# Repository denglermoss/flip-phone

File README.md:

# Custom Phone Project

## Overview

Designing and building a custom cell phone from scratch — hardware (PCB, electronics), embedded firmware, cellular communication, and eventually mechanical/enclosure design. Candybar / single-board form factor (locked 2026-08-16 — flip/clamshell deferred to v2). Long-term vision: the phone is the hub of a personal ecosystem of USB-connected devices. See `docs/ref/problem-definition.md` for full architecture, MVP, risks, and ecosystem vision.

## Goals

- **Learning / Portfolio**: Deepen hardware and embedded systems skills; build something impressive.
- **Actually Usable**: End goal is a device that can make real phone calls on a real cellular network.
- **The Challenge**: Push beyond prior experience (microcontrollers, simple PCBs) into RF, cellular comms, power management, and eventually mechanical integration.

## Scope

### In Scope
- Custom PCB design (candybar / single-board — display via ZIF connector, no hinge flex)
- Microcontroller + off-the-shelf cellular module architecture
- Firmware: call handling, UI, contacts, power management
- Making real phone calls on a real network
- Mechanical/enclosure design (deferred — decided after electronics are proven)
- Hardware selection constrained to preserve USB connectivity for future ecosystem modules

### Out of Scope (for now)
- Custom cellular modem / baseband processor design
- FCC certification (prototype stage; revisit if moving toward production)
- App store, browser, or smartphone features (camera IS included on rev1 — see `docs/ref/project-log.md` 2026-08-16)
- Custom OS (will use RTOS or bare metal)
- Ecosystem module design (car system, etc.) — future projects, not this one

## Documentation

Full doc index and source-of-truth assignments in `AGENTS.md`. Key docs:

- `docs/ref/problem-definition.md` — architecture, MVP, risks, ecosystem vision
- `docs/ref/requirements.md` — functional & non-functional requirements
- `docs/ref/constraints.md` — technical, budget, regulatory constraints
- `docs/ref/project-log.md` — decision log (dated), phase breakdown
- `docs/ref/bom.md` — bill of materials with prices and links
- `docs/work/` — active planning docs (block-diagram, pin assignment, task tracker, schematic completion plan, UI design)
- `docs/archive/` — completed/superseded plans + all revisit prompts

## Status

**Phase 1 (Research & Component Selection) — Complete.** All guiding hardware decisions locked: MCU (STM32H743ZI), modem (SIM7600NA-H), codec (ALC5651-CG), display (ST7789V SPI TFT), keypad (SMD tactile switches), USB architecture (modem-direct tethering, no ULPI). Zephyr development environment set up (2026-06-29).

**Phase 2 (HAT-Based Prototype) — Complete.** MVP achieved (2026-07-13): MCU firmware places and receives VoLTE calls with audio on Mint LTE. Keypad integrated + verified (2026-07-18): standalone dialer — user types phone numbers and places real calls with no PC involvement. See `docs/ref/project-log.md` Phase Breakdown.

**Phase 3 (Schematic Design) — In Progress (2026-07-28).** All parts sourced with KiCad models (no consignment). Schematic approach: flat sheet + global labels, MPCIe modem form factor (primary), LGA fallback. **Per-sheet progress** (see `docs/work/schematic-completion-plan.md` for details): Power ✅, MCU ~92%, Modem ~90%, Codec ✅ (restored), Keypad ✅, Display main ~80% (backlight FET pending), Display daughter ~70%, SIM/SD ✅. ERC: 0 errors, 15 warnings. Remaining work tracked in `docs/work/schematic-completion-plan.md`; full Phase 3-5 plan in `docs/work/task-tracker.md`.

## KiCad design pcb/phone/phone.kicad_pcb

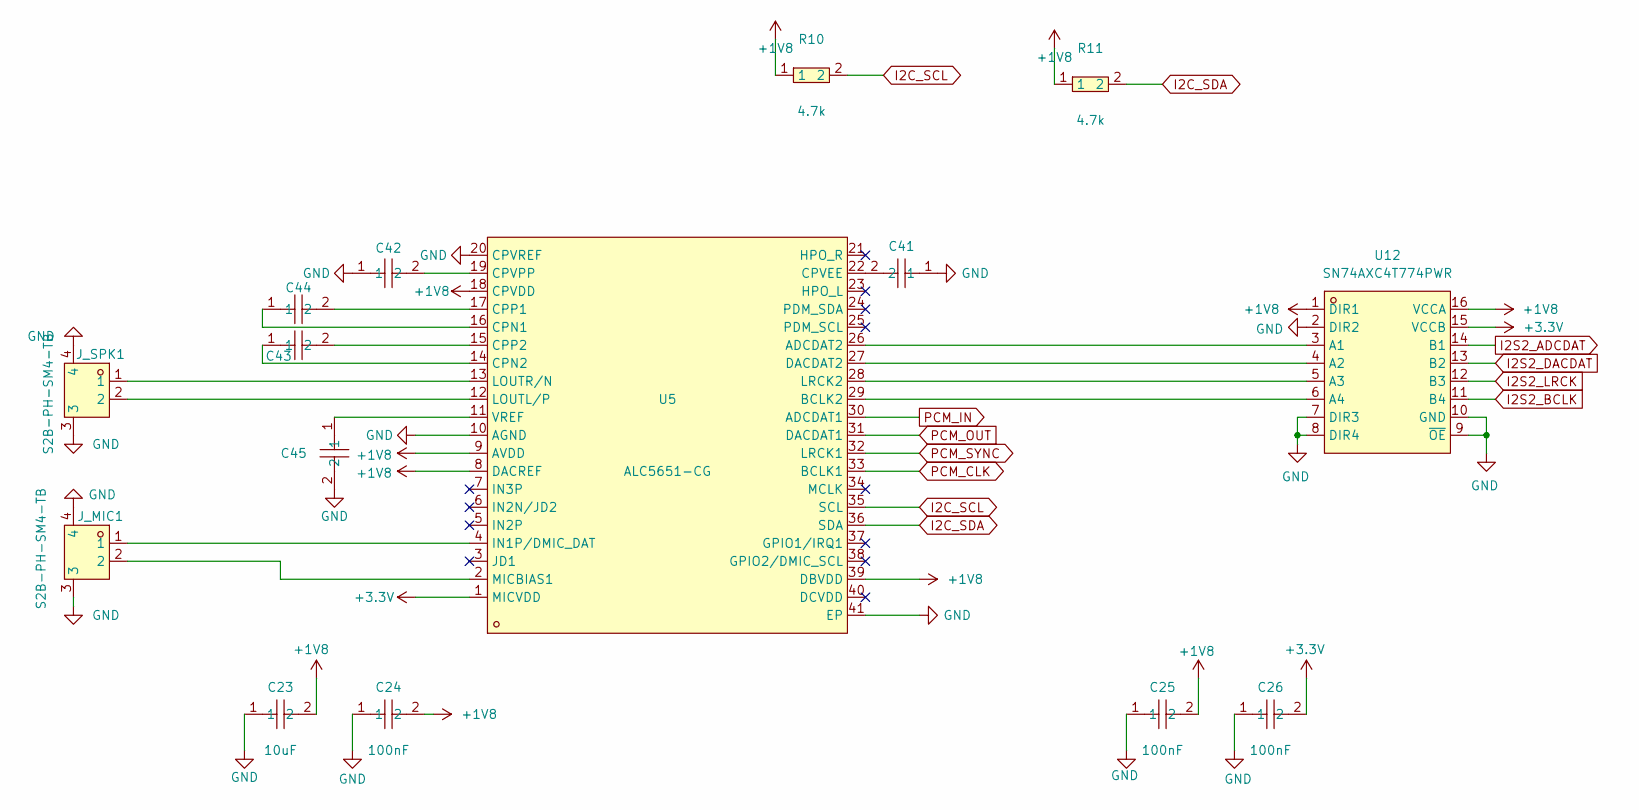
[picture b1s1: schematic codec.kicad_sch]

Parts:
C23: 10uF; C0805
C24, C25, C26: 100nF; C0603
C41, C42, C43, C44: CC0603KRX5R8BB225; C0603; MPN CC0603KRX5R8BB225; LCSC Part C309478
C45: GRM188R61C475KE11D; C0603; MPN GRM188R61C475KE11D; LCSC Part C77045
J_MIC1: S2B-PH-SM4-TB; CONN-SMD_P2.00_S2B-PH-SM4-TB-LF-SN
J_SPK1: S2B-PH-SM4-TB; CONN-SMD_P2.00_S2B-PH-SM4-TB-LF-SN
R10, R11: 4.7k; R0603
U5: ALC5651-CG; QFN-40_L5.0-W5.0-P0.40-BL-EP3.7
U12: SN74AXC4T774PWR; TSSOP-16_L5.0-W4.4-P0.65-LS6.4-TL; MPN SN74AXC4T774PWR; LCSC Part C1849453

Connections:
+1V8: C23.2, C24.2, C25.2, R10.1, R11.1, U5.8 (DACREF), U5.9 (AVDD), U5.18 (CPVDD), U5.39 (DBVDD), U12.1 (DIR1), U12.16 (VCCA); also elsewhere on the board
+3.3V: C26.2, U5.1 (MICVDD), U12.15 (VCCB); also elsewhere on the board
GND: C23.1, C24.1, C25.1, C26.1, C41.1, C42.1, C45.2, J_MIC1.3, J_MIC1.4, J_SPK1.3, J_SPK1.4, U5.10 (AGND), U5.20 (CPVREF), U5.41 (EP), U12.2 (DIR2), U12.7 (DIR3), U12.8 (DIR4), U12.9 (~OE), U12.10 (GND); also elsewhere on the board
I2C_SCL: R10.2, U5.35 (SCL); also elsewhere on the board
I2C_SDA: R11.2, U5.36 (SDA); also elsewhere on the board
I2S2_ADCDAT: U12.14 (B1); also elsewhere on the board
I2S2_BCLK: U12.11 (B4); also elsewhere on the board
I2S2_DACDAT: U12.13 (B2); also elsewhere on the board
I2S2_LRCK: U12.12 (B3); also elsewhere on the board
unnamed: C44.1, U5.16 (CPN1)
unnamed: C43.1, U5.14 (CPN2)
unnamed: C44.2, U5.17 (CPP1)
unnamed: C43.2, U5.15 (CPP2)
unnamed: C41.2, U5.22 (CPVEE)
unnamed: C42.2, U5.19 (CPVPP)
unnamed: J_MIC1.1, U5.4 (IN1P/DMIC_DAT)
unnamed: J_SPK1.2, U5.12 (LOUTL/P)
unnamed: J_SPK1.1, U5.13 (LOUTR/N)
unnamed: J_MIC1.2, U5.2 (MICBIAS1)
unnamed: C45.1, U5.11 (VREF)
unnamed: U5.26 (ADCDAT2), U12.3 (A1)
unnamed: U5.27 (DACDAT2), U12.4 (A2)
unnamed: U5.28 (LRCK2), U12.5 (A3)
unnamed: U5.29 (BCLK2), U12.6 (A4)
PCM_CLK: U5.33 (BCLK1); also elsewhere on the board
PCM_IN: U5.30 (ADCDAT1); also elsewhere on the board
PCM_OUT: U5.31 (DACDAT1); also elsewhere on the board
PCM_SYNC: U5.32 (LRCK1); also elsewhere on the board

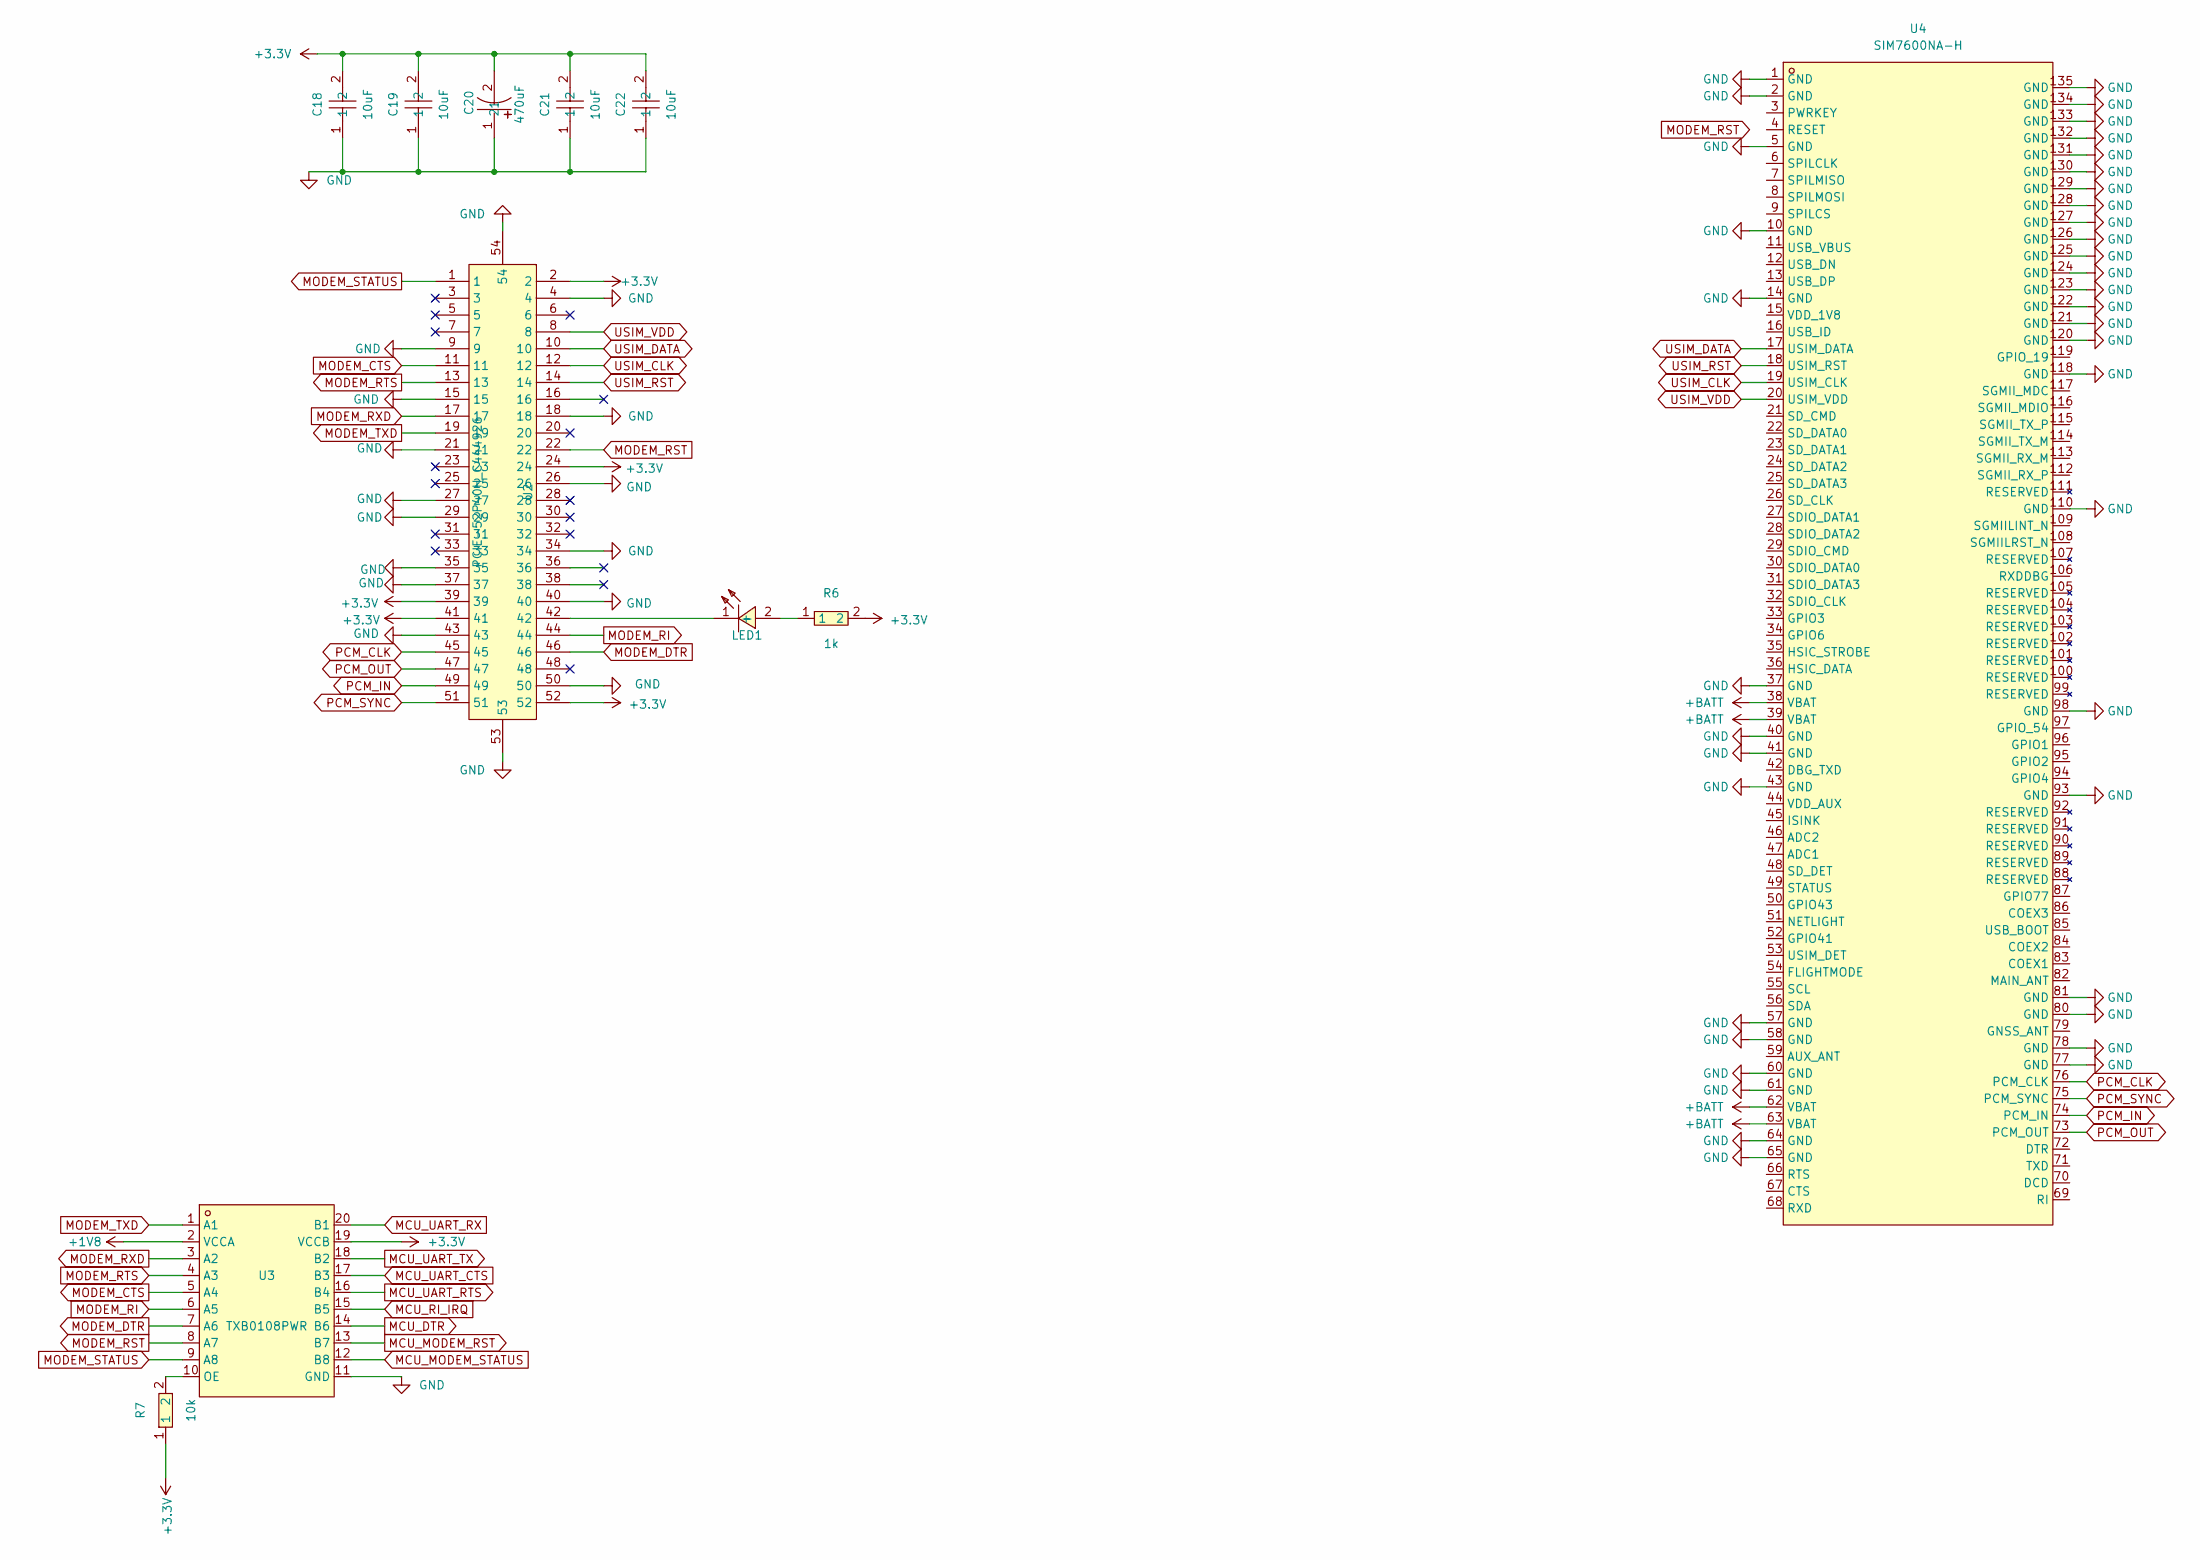
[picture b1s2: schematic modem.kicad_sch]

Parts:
C18, C19, C21, C22: 10uF; C0805
C20: 470uF; CAP-SMD_L7.3-W4.3
LED1: LTST-C191TBKT; LED0603-RD; MPN LTST-C191TBKT; LCSC Part C99290
R6: 1k; R0603
R7: 10k; R0603
U2: PCIE-52P40H_C444926; PCIE-SMD_PCIE-52P40H-1
U3: TXB0108PWR; TSSOP-20_L6.5-W4.4-P0.65-LS6.4-BL
U4: SIM7600NA-H; COMM-SMD_L13.0-W13.0-P1.0_SIM7600NA-H; MPN SIM7600NA-H; LCSC Part C5380303

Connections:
+1V8: U3.2 (VCCA); also elsewhere on the board
+3.3V: C18.2, C19.2, C20.2, C21.2, C22.2, R6.2, R7.1, U2.2, U2.24, U2.39, U2.41, U2.52, U3.19 (VCCB); also elsewhere on the board
GND: C18.1, C19.1, C20.1, C21.1, C22.1, U2.4, U2.9, U2.15, U2.18, U2.21, U2.26, U2.27, U2.29, U2.34, U2.35, U2.37, U2.40, U2.43, U2.50, U2.53, U2.54, U3.11 (GND), U4.1 (GND), U4.2 (GND), U4.5 (GND), U4.10 (GND), U4.14 (GND), U4.37 (GND), U4.40 (GND), U4.41 (GND), U4.43 (GND), U4.57 (GND), U4.58 (GND), U4.60 (GND), U4.61 (GND), U4.64 (GND), U4.65 (GND), U4.77 (GND), U4.78 (GND), U4.80 (GND), U4.81 (GND), U4.93 (GND), U4.98 (GND), U4.110 (GND), U4.118 (GND), U4.120 (GND), U4.121 (GND), U4.122 (GND), U4.123 (GND), U4.124 (GND), U4.125 (GND), U4.126 (GND), U4.127 (GND), U4.128 (GND), U4.129 (GND), U4.130 (GND), U4.131 (GND), U4.132 (GND), U4.133 (GND), U4.134 (GND), U4.135 (GND); also elsewhere on the board
MCU_DTR: U3.14 (B6); also elsewhere on the board
MCU_MODEM_RST: U3.13 (B7); also elsewhere on the board
MCU_MODEM_STATUS: U3.12 (B8); also elsewhere on the board
MCU_RI_IRQ: U3.15 (B5); also elsewhere on the board
MCU_UART_CTS: U3.17 (B3); also elsewhere on the board
MCU_UART_RTS: U3.16 (B4); also elsewhere on the board
MCU_UART_RX: U3.20 (B1); also elsewhere on the board
MCU_UART_TX: U3.18 (B2); also elsewhere on the board
MODEM_CTS: U2.11, U3.5 (A4)
MODEM_DTR: U2.46, U3.7 (A6)
MODEM_RI: U2.44, U3.6 (A5)
MODEM_RST: U2.22, U3.8 (A7)
MODEM_RTS: U2.13, U3.4 (A3)
MODEM_RXD: U2.17, U3.3 (A2)
MODEM_STATUS: U2.1, U3.9 (A8)
MODEM_TXD: U2.19, U3.1 (A1)
unnamed: LED1.2 (+), R6.1
unnamed: LED1.1 (-), U2.42
unnamed: R7.2, U3.10 (OE)
unnamed: U4.38 (VBAT), U4.39 (VBAT), U4.62 (VBAT), U4.63 (VBAT)
PCM_CLK: U2.45, U4.76 (PCM_CLK); also elsewhere on the board
PCM_IN: U2.49, U4.74 (PCM_IN); also elsewhere on the board
PCM_OUT: U2.47, U4.73 (PCM_OUT); also elsewhere on the board
PCM_SYNC: U2.51, U4.75 (PCM_SYNC); also elsewhere on the board
USIM_CLK: U2.12, U4.19 (USIM_CLK); also elsewhere on the board
USIM_DATA: U2.10, U4.17 (USIM_DATA); also elsewhere on the board
USIM_RST: U2.14, U4.18 (USIM_RST); also elsewhere on the board
USIM_VDD: U2.8, U4.20 (USIM_VDD); also elsewhere on the board

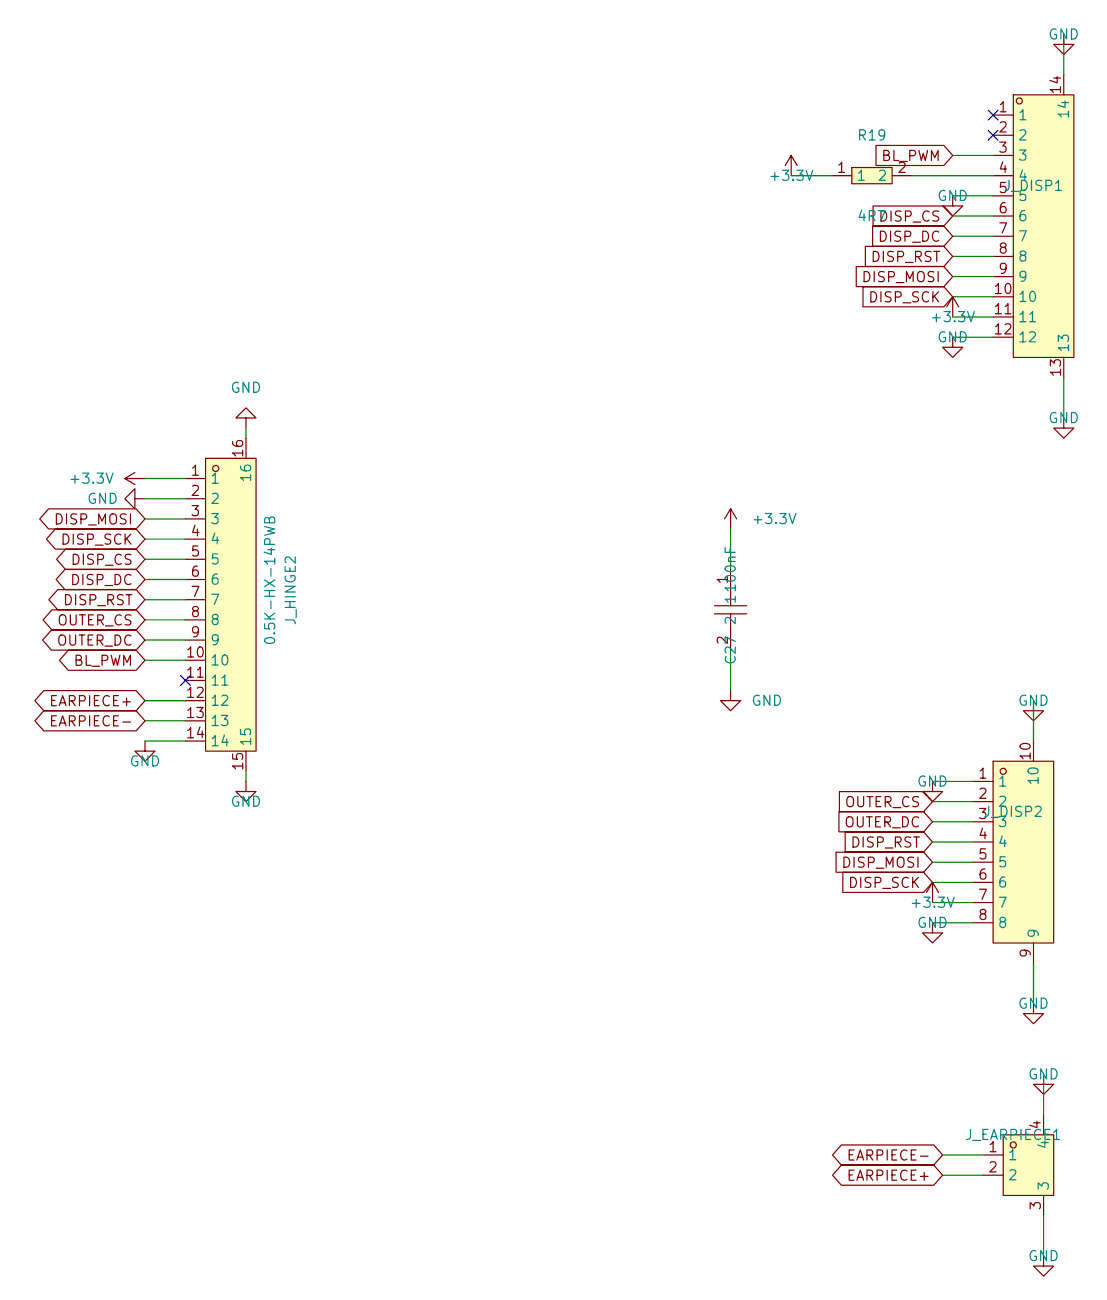
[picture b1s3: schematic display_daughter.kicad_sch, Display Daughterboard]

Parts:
C27: 100nF; C0603
J_DISP1: 0.5K-HX-12PWB; FPC-SMD_12P-P0.50_HDGC_0.5K-HX-12PWB
J_DISP2: 0.5K-HX-8PWB; FPC-SMD_8P-P0.50_HDGC_0.5K-HX-8PWB
J_EARPIECE1: S2B-PH-SM4-TB; CONN-SMD_P2.00_S2B-PH-SM4-TB-LF-SN
J_HINGE2: 0.5K-HX-14PWB; FPC-SMD_14P-P0.50_HDGC_0.5K-HX-14PWB
R19: 4R7; R0603

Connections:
+3.3V: C27.1, J_DISP1.11, J_DISP2.7, J_HINGE2.1, R19.1; also elsewhere on the board
BL_PWM: J_DISP1.3, J_HINGE2.10; also elsewhere on the board
DISP_CS: J_DISP1.6, J_HINGE2.5; also elsewhere on the board
DISP_DC: J_DISP1.7, J_HINGE2.6; also elsewhere on the board
DISP_MOSI: J_DISP1.9, J_DISP2.5, J_HINGE2.3; also elsewhere on the board
DISP_RST: J_DISP1.8, J_DISP2.4, J_HINGE2.7; also elsewhere on the board
DISP_SCK: J_DISP1.10, J_DISP2.6, J_HINGE2.4; also elsewhere on the board
EARPIECE+: J_EARPIECE1.2, J_HINGE2.12; also elsewhere on the board
EARPIECE-: J_EARPIECE1.1, J_HINGE2.13; also elsewhere on the board
GND: C27.2, J_DISP1.5, J_DISP1.12, J_DISP1.13, J_DISP1.14, J_DISP2.1, J_DISP2.8, J_DISP2.9, J_DISP2.10, J_EARPIECE1.3, J_EARPIECE1.4, J_HINGE2.2, J_HINGE2.14, J_HINGE2.15, J_HINGE2.16; also elsewhere on the board
unnamed: J_DISP1.4, R19.2
OUTER_CS: J_DISP2.2, J_HINGE2.8; also elsewhere on the board
OUTER_DC: J_DISP2.3, J_HINGE2.9; also elsewhere on the board

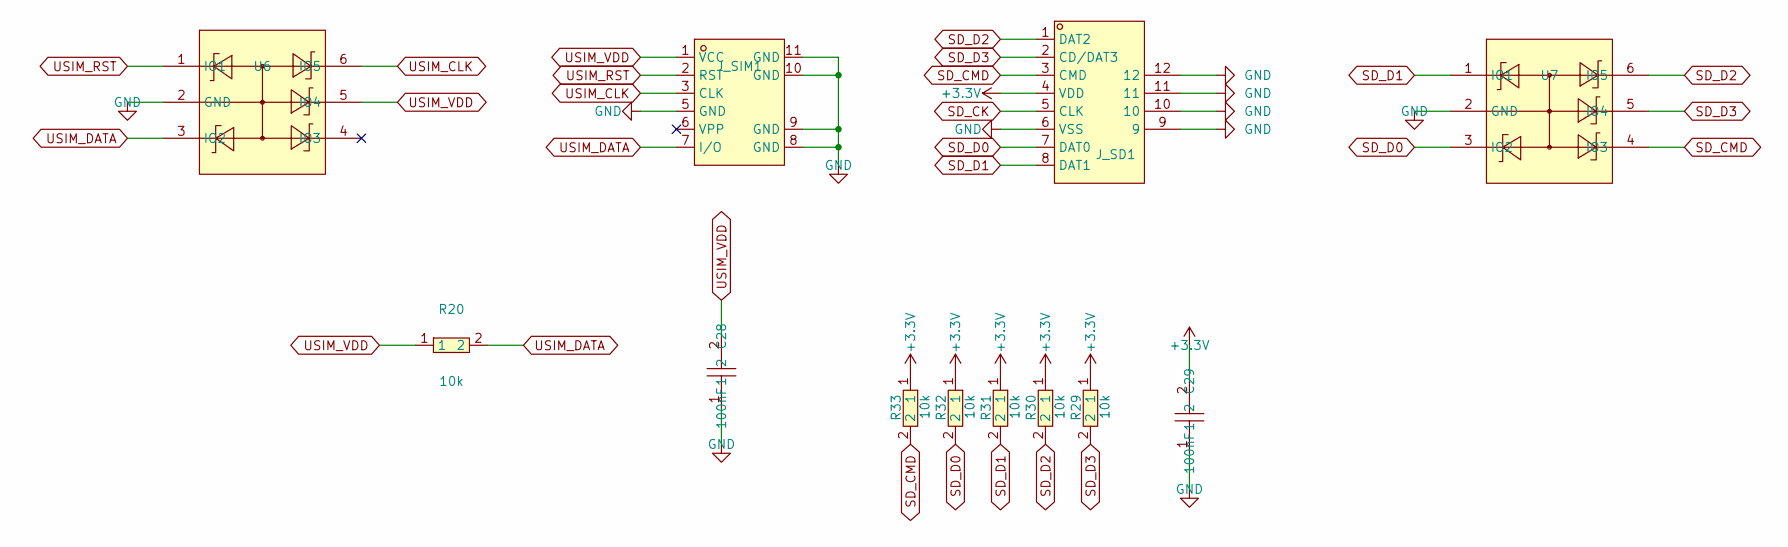
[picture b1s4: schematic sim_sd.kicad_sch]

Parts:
C28, C29: 100nF; C0603
J_SD1: 472192001; TF-SMD_472192001
J_SIM1: NANOSIMXG6PH1.35; SIM-SMD_NANO-SIM-XG6P-H1.35
R20, R29, R30, R31, R32, R33: 10k; R0603
U6, U7: ESDA6V1-5SC6; SOT-23-6_L2.9-W1.6-P0.95-LS2.8-BR

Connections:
+3.3V: C29.2, J_SD1.4 (VDD), R29.1, R30.1, R31.1, R32.1, R33.1; also elsewhere on the board
GND: C28.1, C29.1, J_SD1.6 (VSS), J_SD1.9, J_SD1.10, J_SD1.11, J_SD1.12, J_SIM1.5 (GND), J_SIM1.8 (GND), J_SIM1.9 (GND), J_SIM1.10 (GND), J_SIM1.11 (GND), U6.2 (GND), U7.2 (GND); also elsewhere on the board
SD_CK: J_SD1.5 (CLK); also elsewhere on the board
SD_CMD: J_SD1.3 (CMD), R33.2, U7.4 (IO3); also elsewhere on the board
SD_D0: J_SD1.7 (DAT0), R32.2, U7.3 (IO2); also elsewhere on the board
SD_D1: J_SD1.8 (DAT1), R31.2, U7.1 (IO1); also elsewhere on the board
SD_D2: J_SD1.1 (DAT2), R30.2, U7.6 (IO5); also elsewhere on the board
SD_D3: J_SD1.2 (CD/DAT3), R29.2, U7.5 (IO4); also elsewhere on the board
USIM_CLK: J_SIM1.3 (CLK), U6.6 (IO5); also elsewhere on the board
USIM_DATA: J_SIM1.7 (I/O), R20.2, U6.3 (IO2); also elsewhere on the board
USIM_RST: J_SIM1.2 (RST), U6.1 (IO1); also elsewhere on the board
USIM_VDD: C28.2, J_SIM1.1 (VCC), R20.1, U6.5 (IO4); also elsewhere on the board

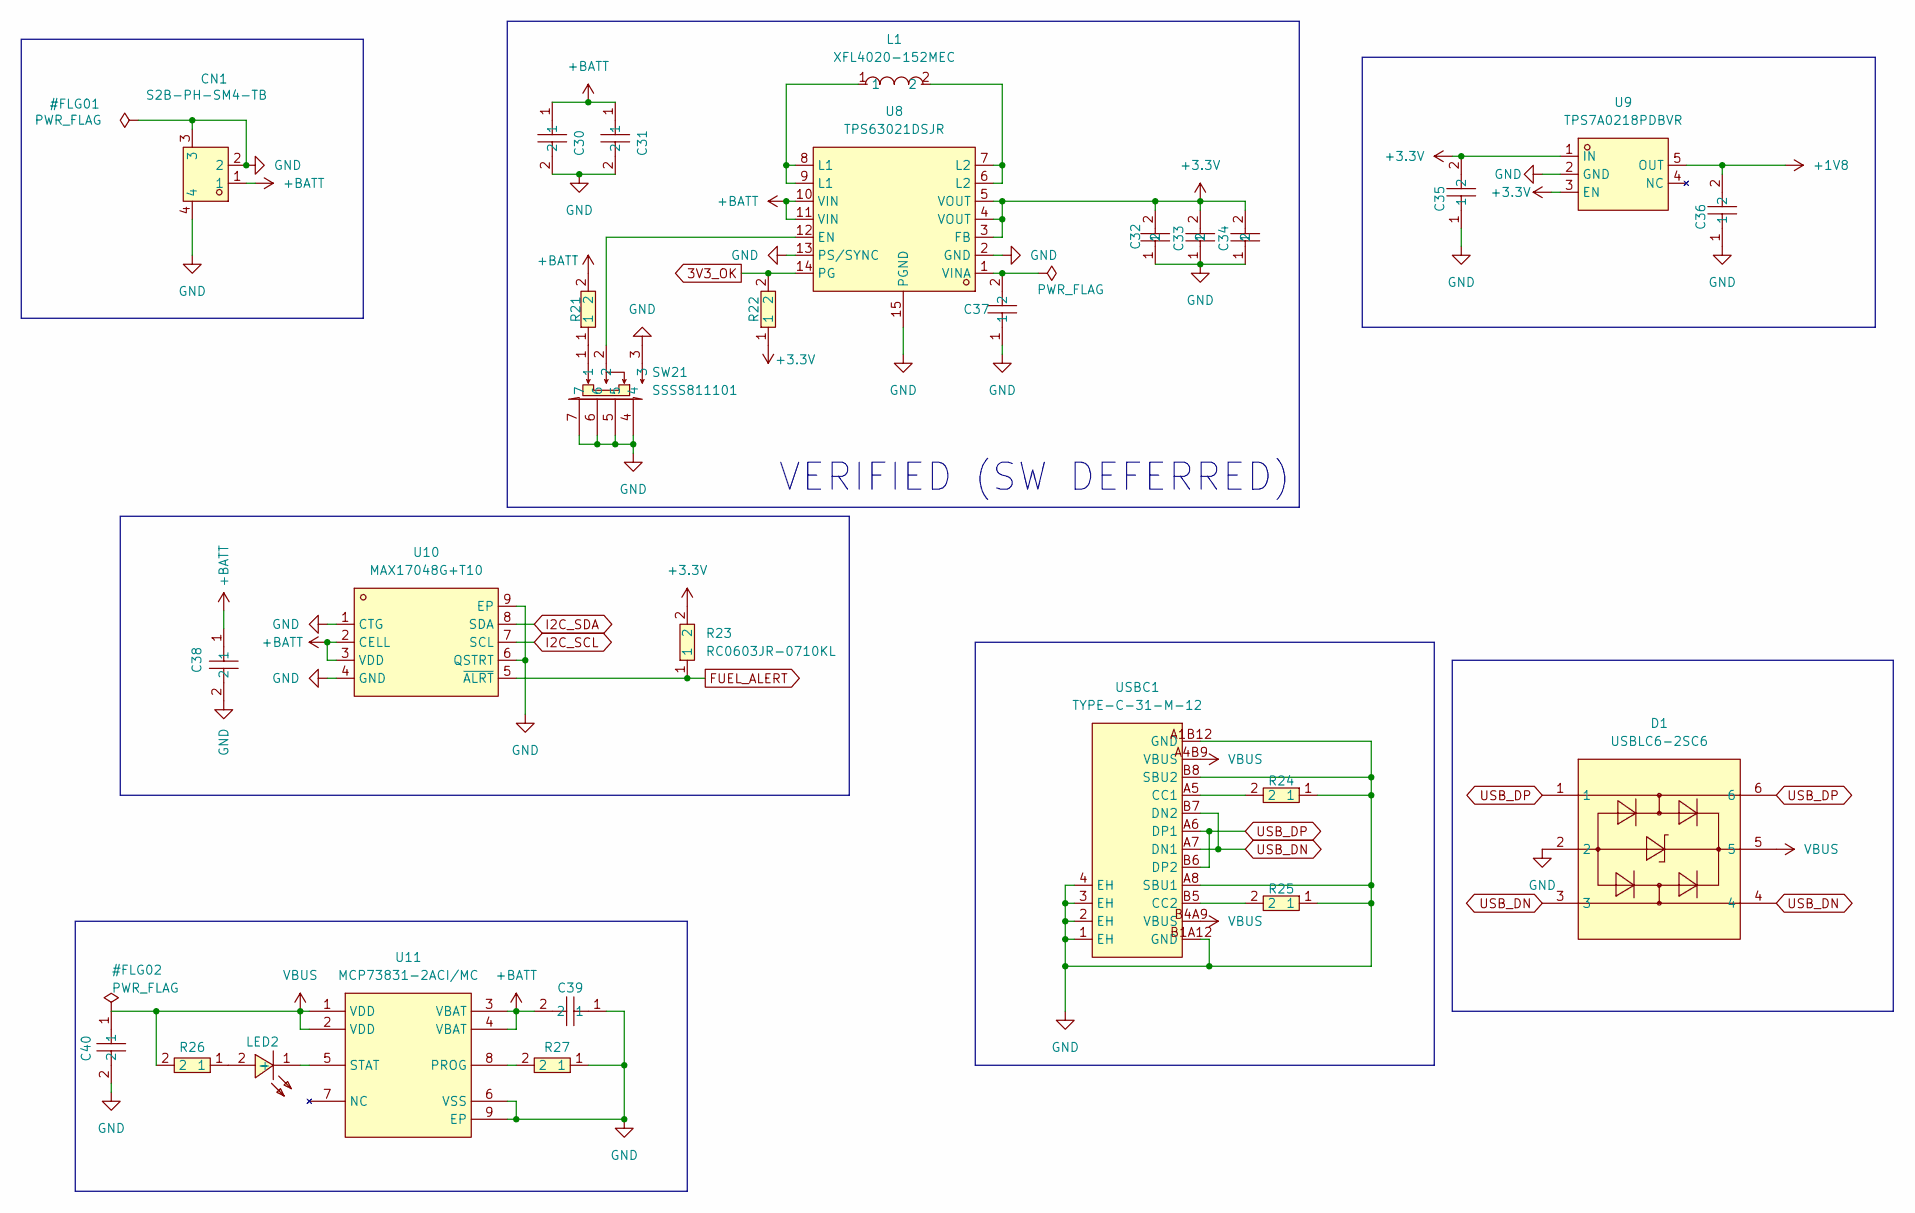
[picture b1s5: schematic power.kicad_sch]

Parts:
C30, C31: GRM21BR61H106KE43L; C0805; MPN GRM21BR61H106KE43L; LCSC Part C440198
C32, C33, C34: GRM21BR61A226ME51L; C0805; MPN GRM21BR61A226ME51L; LCSC Part C77074
C35, C36: GRM188R61C105KA93D; C0603; MPN GRM188R61C105KA93D; LCSC Part C77404
C37, C38: CC0603KRX7R9BB104; C0603; MPN CC0603KRX7R9BB104; LCSC Part C14663
C39, C40: GRM188R61C475KE11D; C0603; MPN GRM188R61C475KE11D; LCSC Part C77045
CN1: S2B-PH-SM4-TB; CONN-SMD_P2.00_S2B-PH-SM4-TB-LF-SN; MPN S2B-PH-SM4-TB(LF)(SN); LCSC Part C295747
D1: USBLC6-2SC6; SOT-23-6_L2.9-W1.6-P0.95-LS2.8-BL; MPN USBLC6-2SC6; LCSC Part C7519
L1: XFL4020-152MEC; IND-SMD_L4.0-W4.0-A; MPN XFL4020-152MEC; LCSC Part C3033018
LED2: LTST-C191TBKT; LED0603-RD; MPN LTST-C191TBKT; LCSC Part C99290
R21: RC0603JR-071ML; R0603; MPN RC0603JR-071ML; LCSC Part C107698
R22, R23: RC0603JR-0710KL; R0603; MPN RC0603JR-0710KL; LCSC Part C99198
R24, R25: RC0603FR-075K1L; R0603; MPN RC0603FR-075K1L; LCSC Part C105580
R26: RC0603JR-07470RL; R0603; MPN RC0603JR-07470RL; LCSC Part C114433
R27: RC0603FR-072KL; R0603; MPN RC0603FR-072KL; LCSC Part C105576
SW21: SSSS811101; SW-SMD_SSSS811101; MPN SSSS811101; LCSC Part C109335
U8: TPS63021DSJR; VSON-14_L4.0-W3.0-P0.50-BL-EP_TI_DSJ; MPN TPS63021DSJR; LCSC Part C202140
U9: TPS7A0218PDBVR; SOT-23-5_L2.9-W1.6-P0.95-LS2.8-BL; MPN TPS7A0218PDBVR; LCSC Part C3748843
U10: MAX17048G+T10; TDFN-8_L2.0-W2.0-P0.50-BL-EP1.2; MPN MAX17048G+T10; LCSC Part C2682616
U11: MCP73831-2ACI/MC; TDFN-8_L3.0-W2.0-P0.50-BL-EP1.6; MPN MCP73831-2ACI/MC; LCSC Part C150772
USBC1: TYPE-C-31-M-12; USB-C_SMD-TYPE-C-31-M-12_1; MPN TYPE-C-31-M-12; LCSC Part C165948

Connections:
3V3_OK: R22.2, U8.14 (PG); also elsewhere on the board
+1V8: C36.2, U9.5 (OUT); also elsewhere on the board
+3.3V: C32.2, C33.2, C34.2, C35.2, R22.1, R23.2, U8.3 (FB), U8.4 (VOUT), U8.5 (VOUT), U9.1 (IN), U9.3 (EN); also elsewhere on the board
+BATT: C30.1, C31.1, C38.1, C39.2, CN1.1, R21.2, U8.10 (VIN), U8.11 (VIN), U10.2 (CELL), U10.3 (VDD), U11.3 (VBAT), U11.4 (VBAT)
FUEL_ALERT: R23.1, U10.5 (~ALRT); also elsewhere on the board
GND: C30.2, C31.2, C32.1, C33.1, C34.1, C35.1, C36.1, C37.1, C38.2, C39.1, C40.2, CN1.2, CN1.3, CN1.4, D1.2, R24.1, R25.1, R27.1, SW21.3, SW21.4, SW21.5, SW21.6, SW21.7, U8.2 (GND), U8.13 (PS/SYNC), U8.15 (PGND), U9.2 (GND), U10.1 (CTG), U10.4 (GND), U10.6 (QSTRT), U10.9 (EP), U11.6 (VSS), U11.9 (EP), USBC1.1 (EH), USBC1.2 (EH), USBC1.3 (EH), USBC1.4 (EH), USBC1.A1B12 (GND), USBC1.A8 (SBU1), USBC1.B1A12 (GND), USBC1.B8 (SBU2); also elsewhere on the board
I2C_SCL: U10.7 (SCL); also elsewhere on the board
I2C_SDA: U10.8 (SDA); also elsewhere on the board
unnamed: L1.1, U8.8 (L1), U8.9 (L1)
unnamed: L1.2, U8.6 (L2), U8.7 (L2)
unnamed: LED2.2 (+), R26.1
unnamed: LED2.1 (-), U11.5 (STAT)
unnamed: R21.1, SW21.1
unnamed: SW21.2, U8.12 (EN)
unnamed: C37.2, U8.1 (VINA)
unnamed: R27.2, U11.8 (PROG)
unnamed: R24.2, USBC1.A5 (CC1)
unnamed: R25.2, USBC1.B5 (CC2)
USB_DN: D1.3, D1.4, USBC1.A7 (DN1), USBC1.B7 (DN2); also elsewhere on the board
USB_DP: D1.1, D1.6, USBC1.A6 (DP1), USBC1.B6 (DP2); also elsewhere on the board
VBUS: C40.1, D1.5, R26.2, U11.1 (VDD), U11.2 (VDD), USBC1.A4B9 (VBUS), USBC1.B4A9 (VBUS); also elsewhere on the board

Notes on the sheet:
VERIFIED (SW DEFERRED)

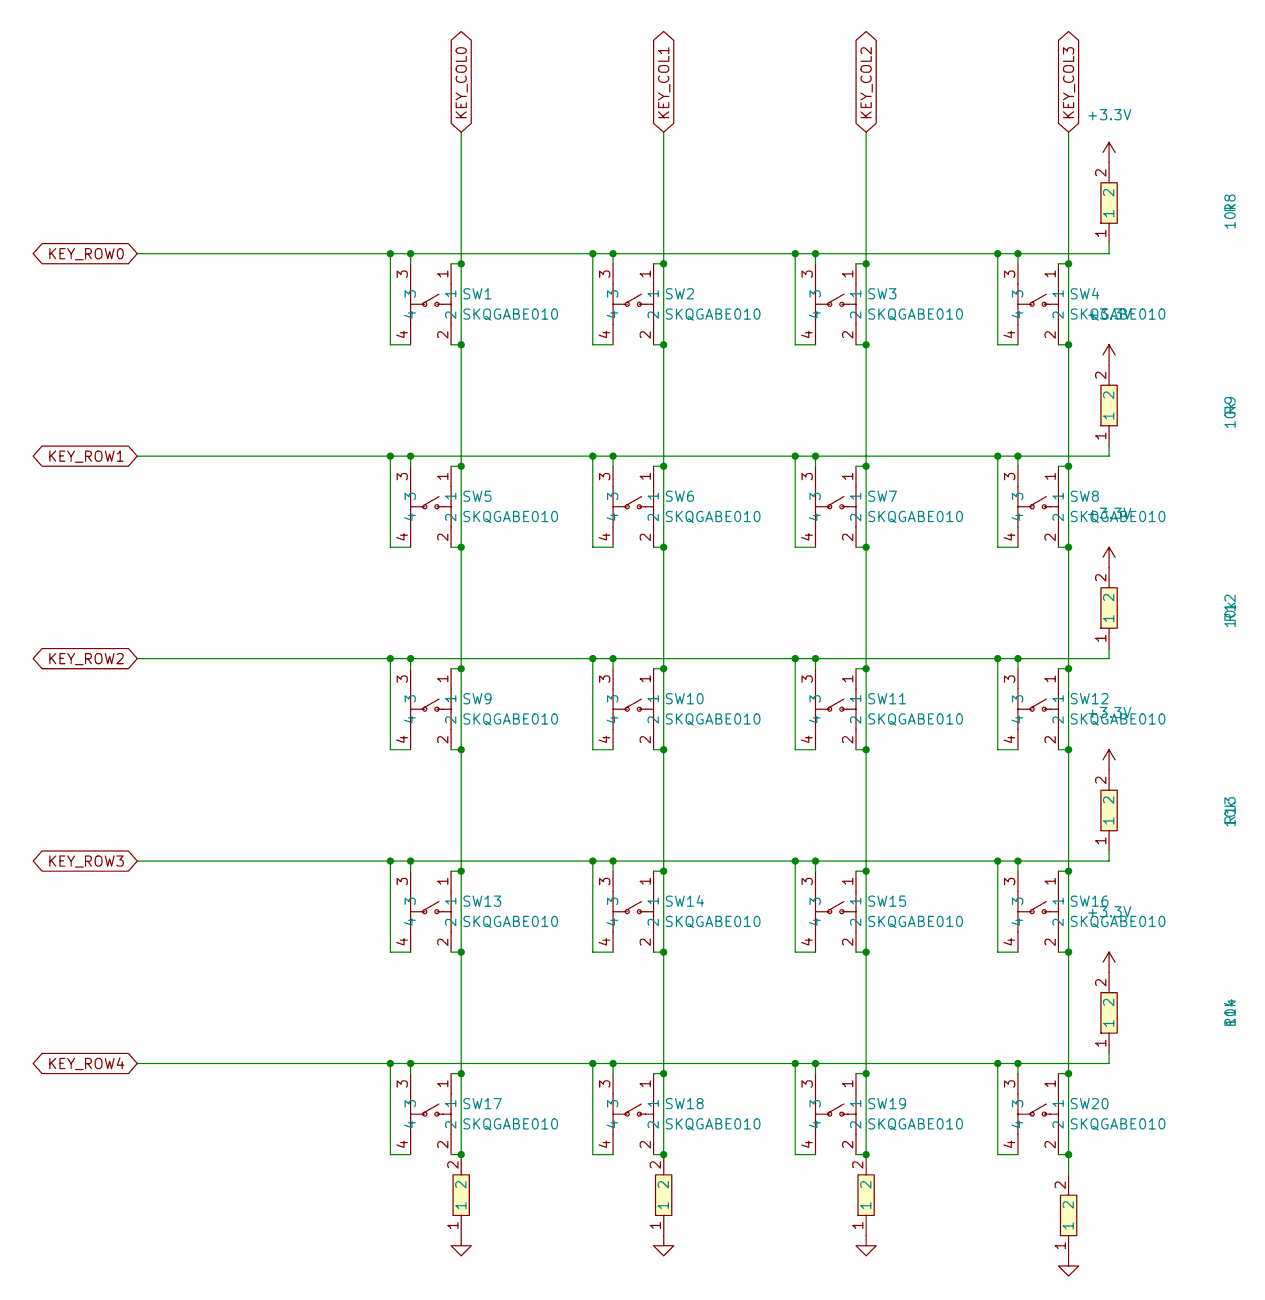
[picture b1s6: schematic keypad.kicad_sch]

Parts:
R8, R9, R12, R13, R14, R15, R16, R17, R18: 10k; R0603
SW1, SW2, SW3, SW4, SW5, SW6, SW7, SW8, SW9, SW10, SW11, SW12, SW13, SW14, SW15, SW16, SW17, SW18, SW19, SW20: SKQGABE010; KEY-SMD_4P-L5.2-W5.2-P3.70-LS6.4; MPN SKQGABE010; LCSC Part C115351

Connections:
+3.3V: R8.2, R9.2, R12.2, R13.2, R14.2; also elsewhere on the board
GND: R15.1, R16.1, R17.1, R18.1; also elsewhere on the board
KEY_COL0: R15.2, SW1.1, SW1.2, SW5.1, SW5.2, SW9.1, SW9.2, SW13.1, SW13.2, SW17.1, SW17.2; also elsewhere on the board
KEY_COL1: R16.2, SW2.1, SW2.2, SW6.1, SW6.2, SW10.1, SW10.2, SW14.1, SW14.2, SW18.1, SW18.2; also elsewhere on the board
KEY_COL2: R17.2, SW3.1, SW3.2, SW7.1, SW7.2, SW11.1, SW11.2, SW15.1, SW15.2, SW19.1, SW19.2; also elsewhere on the board
KEY_COL3: R18.2, SW4.1, SW4.2, SW8.1, SW8.2, SW12.1, SW12.2, SW16.1, SW16.2, SW20.1, SW20.2; also elsewhere on the board
KEY_ROW0: R8.1, SW1.3, SW1.4, SW2.3, SW2.4, SW3.3, SW3.4, SW4.3, SW4.4; also elsewhere on the board
KEY_ROW1: R9.1, SW5.3, SW5.4, SW6.3, SW6.4, SW7.3, SW7.4, SW8.3, SW8.4; also elsewhere on the board
KEY_ROW2: R12.1, SW9.3, SW9.4, SW10.3, SW10.4, SW11.3, SW11.4, SW12.3, SW12.4; also elsewhere on the board
KEY_ROW3: R13.1, SW13.3, SW13.4, SW14.3, SW14.4, SW15.3, SW15.4, SW16.3, SW16.4; also elsewhere on the board
KEY_ROW4: R14.1, SW17.3, SW17.4, SW18.3, SW18.4, SW19.3, SW19.4, SW20.3, SW20.4; also elsewhere on the board
